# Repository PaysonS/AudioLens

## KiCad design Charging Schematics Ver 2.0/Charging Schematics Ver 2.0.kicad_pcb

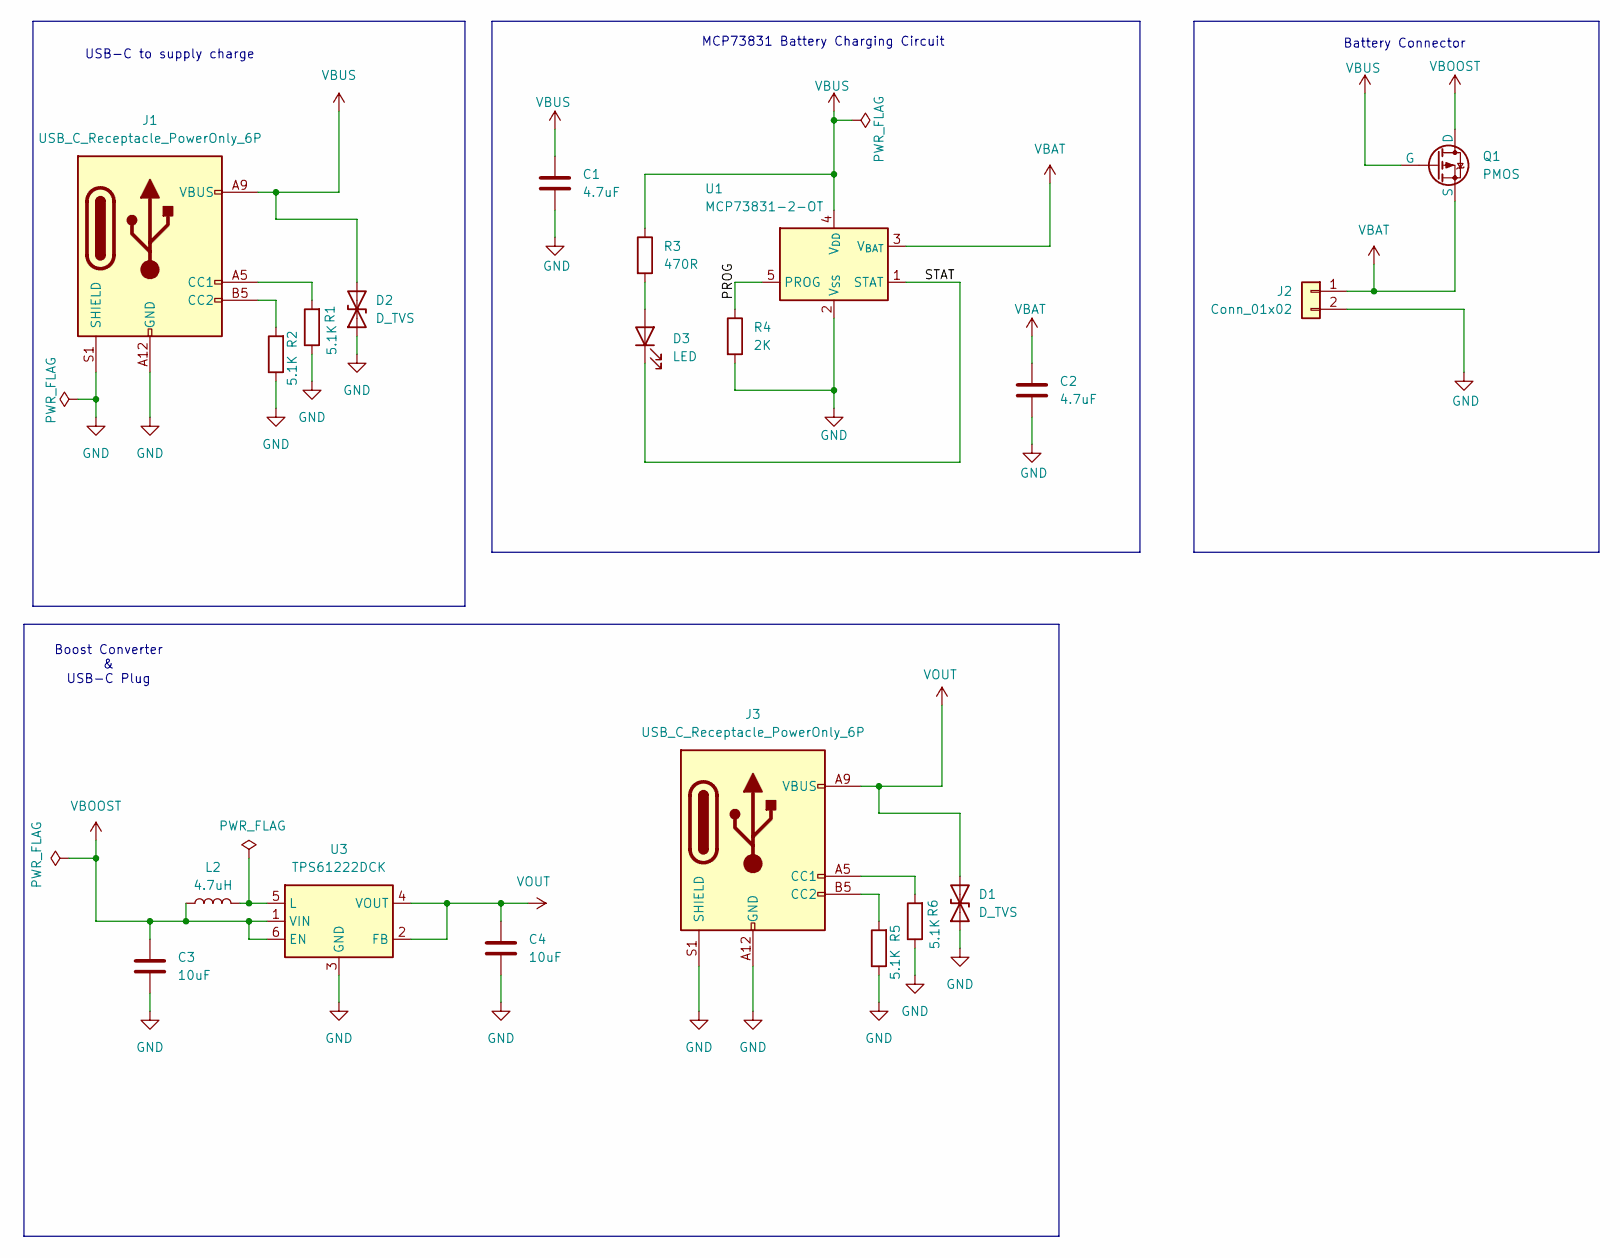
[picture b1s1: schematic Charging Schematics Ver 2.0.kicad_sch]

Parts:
C1, C2: 4.7uF; C_0805_2012Metric_Pad1.18x1.45mm_HandSolder
C3, C4: 10uF; C_0805_2012Metric_Pad1.18x1.45mm_HandSolder
D1, D2: D_TVS; D_SOD-123
D3: LED; LED_0805_2012Metric_Pad1.15x1.40mm_HandSolder
J1, J3: USB_C_Receptacle_PowerOnly_6P; USB_C_Receptacle_GCT_USB4125-xx-x_6P_TopMnt_Horizontal
J2: Conn_01x02; JST_S2B-PH-SM4-TB_LF__SN_
L2: 4.7uH; L_0805_2012Metric_Pad1.15x1.40mm_HandSolder
Q1: PMOS; SOT-23
R1, R2, R5, R6: 5.1K; R_0805_2012Metric_Pad1.20x1.40mm_HandSolder
R3: 470R; R_0805_2012Metric_Pad1.20x1.40mm_HandSolder
R4: 2K; R_0805_2012Metric_Pad1.20x1.40mm_HandSolder
U1: MCP73831-2-OT; SOT-23-5
U3: TPS61222DCK; Texas_R-PDSO-G6

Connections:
/PROG: R4.1, U1.5 (PROG)
/STAT: D3.1 (K), U1.1 (STAT)
GND: C1.2, C2.2, C3.2, C4.2, D1.1 (A1), D2.1 (A1), J1.A12 (GND), J1.B12 (GND), J1.S1 (SHIELD), J2.2, J3.A12 (GND), J3.B12 (GND), J3.S1 (SHIELD), R1.1, R2.1, R4.2, R5.1, R6.1, U1.2 (V_{SS}), U3.3 (GND); also elsewhere on the board
unnamed: D3.2 (A), R3.2
unnamed 4: J1.A5 (CC1), R1.2; also elsewhere on the board
unnamed 5: J1.B5 (CC2), R2.2; also elsewhere on the board
unnamed 6: J3.A5 (CC1), R6.2; also elsewhere on the board
unnamed 7: J3.B5 (CC2), R5.2; also elsewhere on the board
unnamed: L2.2, U3.5 (L)
VBAT: C2.1, J2.1, Q1.3 (S), U1.3 (V_{BAT})
VBOOST: C3.1, L2.1, Q1.1 (D), U3.1 (VIN), U3.6 (EN)
VBUS: C1.1, D2.2 (A2), J1.A9 (VBUS), J1.B9 (VBUS), Q1.2 (G), R3.1, U1.4 (V_{DD}); also elsewhere on the board
VOUT: C4.1, D1.2 (A2), J3.A9 (VBUS), J3.B9 (VBUS), U3.2 (FB), U3.4 (VOUT); also elsewhere on the board

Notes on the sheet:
Battery Connector
USB-C to supply charge
MCP73831 Battery Charging Circuit
Boost Converter & USB-C Plug

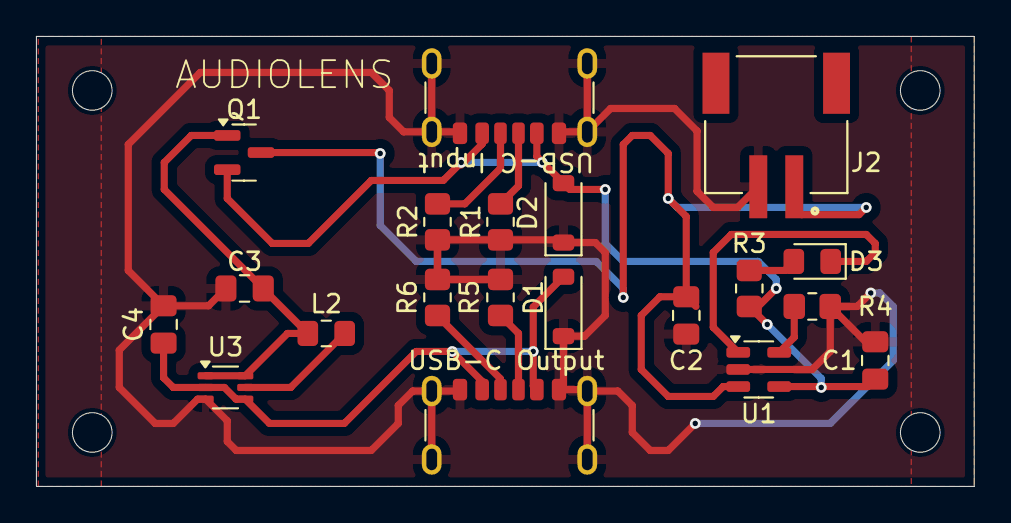
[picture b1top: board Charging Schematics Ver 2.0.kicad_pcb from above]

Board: 2 copper layers, 52.1 x 25.0 mm, 20 parts (0 on the bottom side), 13 nets.

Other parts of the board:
USB-C Input: USB_C_Receptacle_PowerOnly_6P; USB_C_Receptacle_GCT_USB4125-xx-x_6P_TopMnt_Horizontal
USB-C Output: USB_C_Receptacle_PowerOnly_6P; USB_C_Receptacle_GCT_USB4125-xx-x_6P_TopMnt_Horizontal

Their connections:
GND: USB-C Input.A12 (GND), USB-C Input.B12 (GND), USB-C Input.S1 (SHIELD), USB-C Output.A12 (GND), USB-C Output.B12 (GND), USB-C Output.S1 (SHIELD); also elsewhere on the board
unnamed 4: USB-C Input.A5 (CC1); also elsewhere on the board
unnamed 5: USB-C Input.B5 (CC2); also elsewhere on the board
unnamed 6: USB-C Output.A5 (CC1); also elsewhere on the board
unnamed 7: USB-C Output.B5 (CC2); also elsewhere on the board
VBUS: USB-C Input.A9 (VBUS), USB-C Input.B9 (VBUS); also elsewhere on the board
VOUT: USB-C Output.A9 (VBUS), USB-C Output.B9 (VBUS); also elsewhere on the board

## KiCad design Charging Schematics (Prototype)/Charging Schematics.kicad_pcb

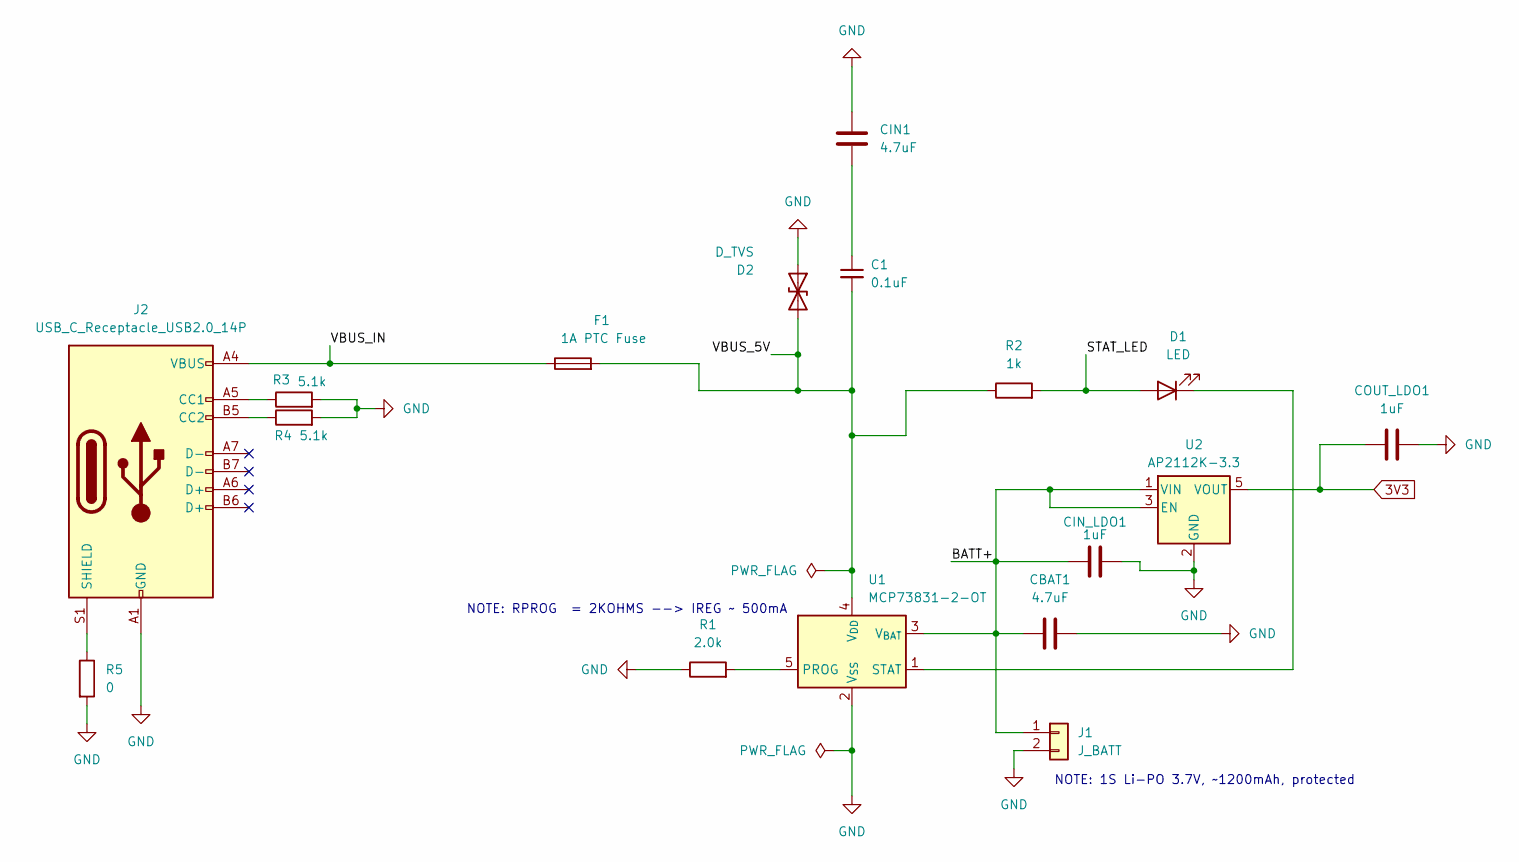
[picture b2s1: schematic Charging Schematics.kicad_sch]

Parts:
C1: 0.1uF; C_0603_1608Metric
CBAT1: 4.7uF; C_0805_2012Metric
CIN1: 4.7uF; C_0805_2012Metric
CIN_LDO1: 1uF; C_0603_1608Metric
COUT_LDO1: 1uF; C_0603_1608Metric
D1: LED; LED_0603_1608Metric
D2: D_TVS; D_SOD-323F
F1: 1A PTC Fuse; Fuse_1206_3216Metric
J1: J_BATT; JST_PH_B2B-PH-K_1x02_P2.00mm_Vertical
J2: USB_C_Receptacle_USB2.0_14P; USB_C_Receptacle_HRO_TYPE-C-31-M-12
R1: 2.0k; R_0603_1608Metric
R2: 1k; R_0603_1608Metric
R3, R4: 5.1k; R_0603_1608Metric
R5: 0; R_0603_1608Metric
U1: MCP73831-2-OT; SOT-23-5
U2: AP2112K-3.3; SOT-23-5

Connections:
3V3: COUT_LDO1.1, U2.5 (VOUT)
/BATT+: CBAT1.1, CIN_LDO1.1, J1.1, U1.3 (V_{BAT}), U2.1 (VIN), U2.3 (EN)
/STAT_LED: D1.2 (A), R2.2
/VBUS_5V: C1.2, D2.2 (A2), F1.2, R2.1, U1.4 (V_{DD})
/VBUS_IN: F1.1, J2.A4 (VBUS), J2.A9 (VBUS), J2.B4 (VBUS), J2.B9 (VBUS)
GND: CBAT1.2, CIN1.1, CIN_LDO1.2, COUT_LDO1.2, D2.1 (A1), J1.2, J2.A1 (GND), J2.A12 (GND), J2.B1 (GND), J2.B12 (GND), R1.1, R3.2, R4.2, R5.2, U1.2 (V_{SS}), U2.2 (GND)
unnamed: C1.1, CIN1.2
unnamed: D1.1 (K), U1.1 (STAT)
unnamed: J2.A5 (CC1), R3.1
unnamed: J2.B5 (CC2), R4.1
unnamed: J2.S1 (SHIELD), R5.1
unnamed: R1.2, U1.5 (PROG)

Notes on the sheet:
NOTE: 1S Li-PO 3.7V, ~1200mAh, protected
NOTE: RPROG = 2KOHMS --> IREG ~ 500mA

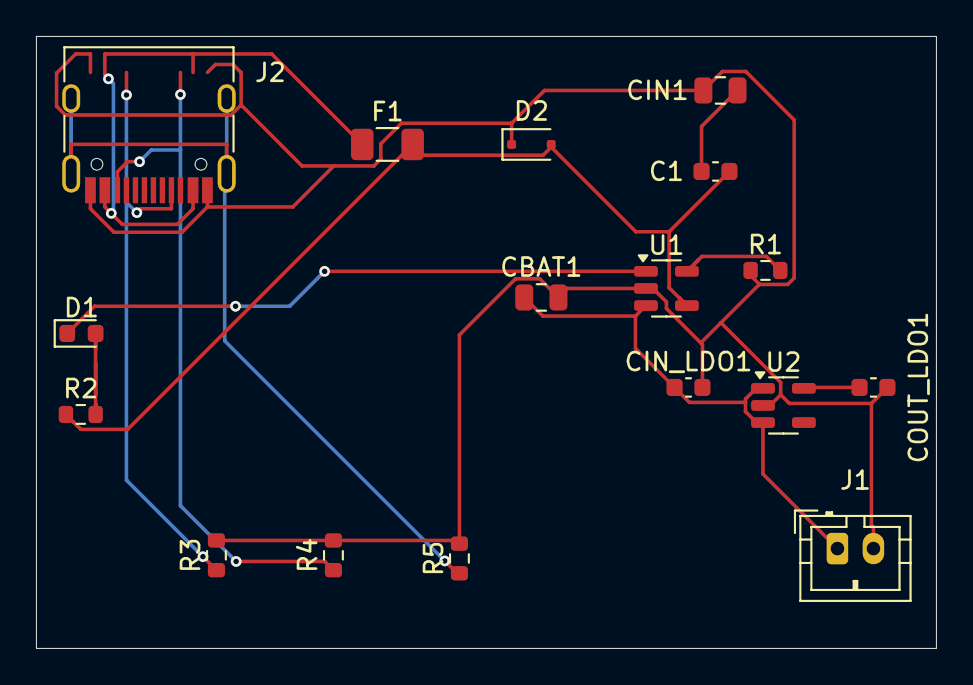
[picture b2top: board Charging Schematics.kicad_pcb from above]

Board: 2 copper layers, 50.0 x 34.0 mm, 17 parts (0 on the bottom side), 12 nets.

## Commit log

2025-12-07 Refactor ONNX model description function
2025-12-07 Refactor training script for ASR model
2025-12-07 Create Fusion 360 file for Glasses Frame
2026-05-15 Add speech server implementation in Server.py
    Implement a speech server using Vosk for speech recognition and Piper for text-to-speech synthesis.
2026-05-15 Add initial ESP32 code for Wi-Fi audio streaming
